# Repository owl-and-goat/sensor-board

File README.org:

#+title: sensor board

* stackup & antenna
see https://jlcpcb.com/impedance; stackup is currently set to 1.6 mm, controlled
impedance, 1 oz copper on all layers, which gives 0.203 mm / 0.008" outer
prepreg thickness for the "no requirement" stackup. board thickness is 1.6 mm ≈
0.062", so we'll be using the first of [[https://www.silabs.com/documents/public/application-notes/an1088-designing-with-pcb-antenna.pdf][these]] reference layouts.

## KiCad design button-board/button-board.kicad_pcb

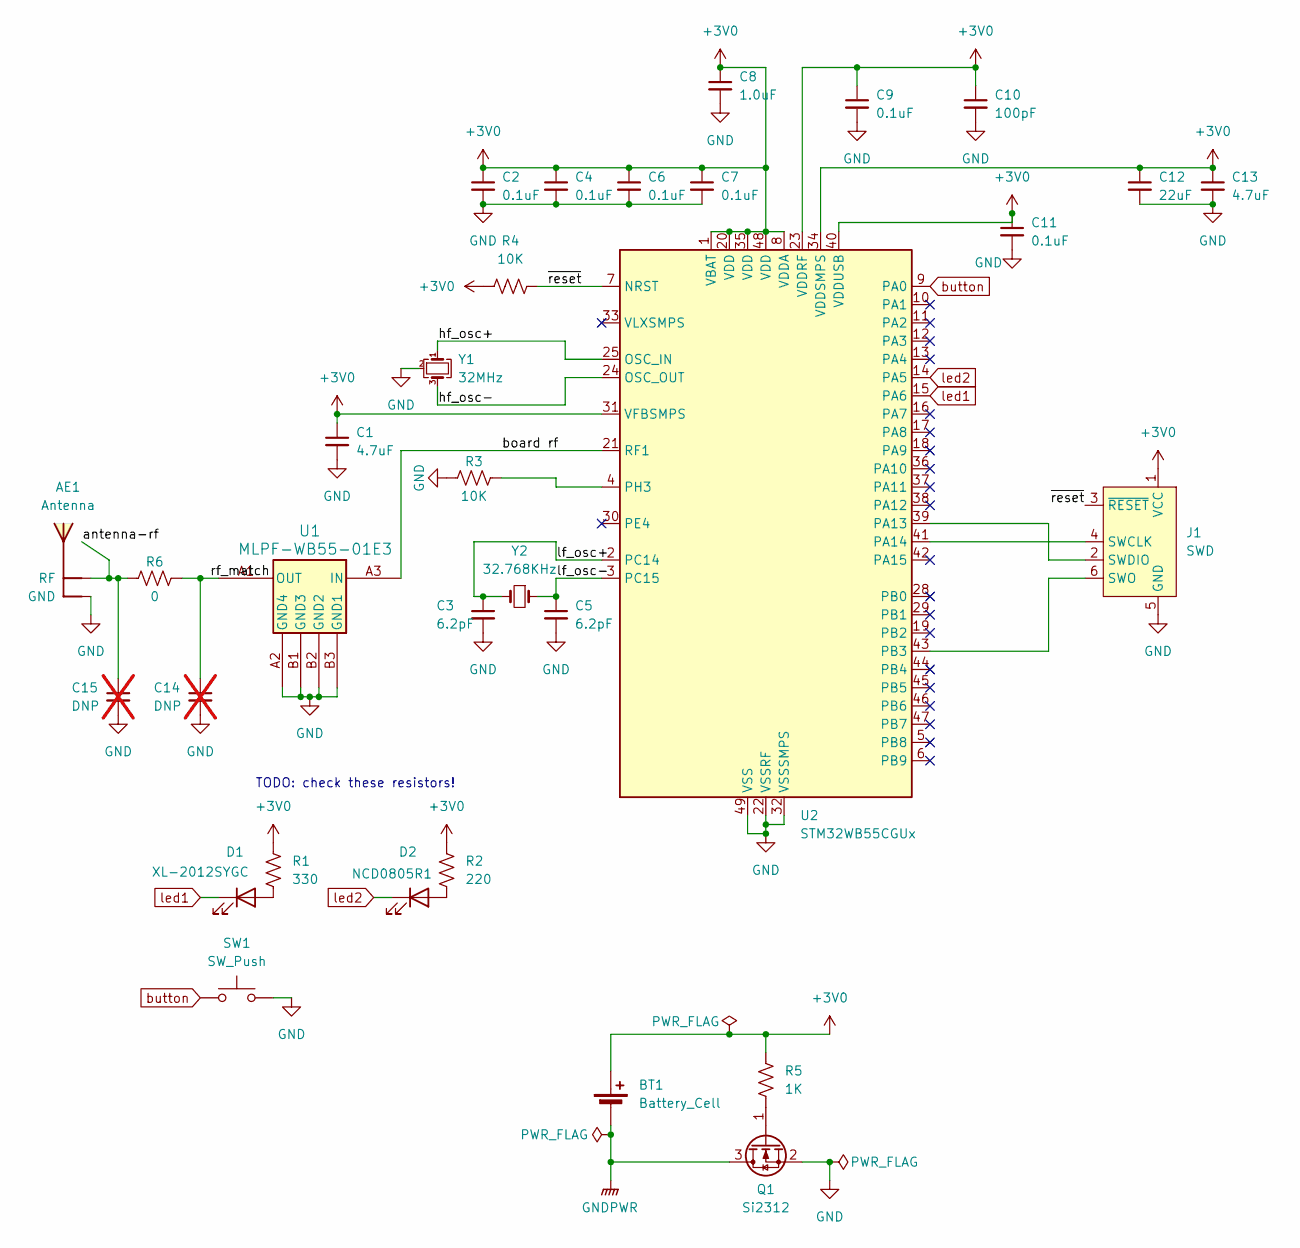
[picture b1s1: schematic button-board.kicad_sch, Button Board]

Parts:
AE1: Antenna; ANT_MIFA_TI_AN043
BT1: Battery_Cell; BatteryHolder_Keystone_3034_1x20mm_SmallPad
C1, C13: 4.7uF; C_0402_1005Metric; LCSC C23733
C2, C4, C6, C7, C9, C11: 0.1uF; C_0402_1005Metric; LCSC C141382
C3, C5: 6.2pF; C_0402_1005Metric
C8: 1.0uF; C_0402_1005Metric; LCSC C52923
C10: 100pF; C_0402_1005Metric; LCSC C1546
C12: 22uF; C_0805_2012Metric
C14, C15: DNP; C_0402_1005Metric; not fitted
D1: XL-2012SYGC; LED_0805_2012Metric; LCSC C965816
D2: NCD0805R1; LED_0805_2012Metric; LCSC C84256
J1: SWD; Tag-Connect_TC2030-IDC-NL_2x03_P1.27mm_Vertical
Q1: Si2312; SOT-23
R1: 330; R_0402_1005Metric; LCSC C25104
R2: 220; R_0402_1005Metric; LCSC C25091
R3, R4: 10K; R_0402_1005Metric; LCSC C25744
R5: 1K; R_0402_1005Metric; LCSC C11702
R6: 0; R_0402_1005Metric; LCSC C17168
SW1: SW_Push; Keystone_5133_KeypadDome_8mm
U1: MLPF-WB55-01E3; MLPF-WB55-01E3_STM; LCSC C2651048
U2: STM32WB55CGUx; QFN-48-1EP_7x7mm_P0.5mm_EP5.6x5.6mm; LCSC C404023
Y1: 32MHz; Crystal_SMD_2016-4Pin_2.0x1.6mm
Y2: 32.768KHz; Crystal_SMD_3215-2Pin_3.2x1.5mm

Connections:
+3V0: BT1.1 (+), C1.1, C2.1, C4.1, C6.1, C7.1, C8.1, C9.1, C10.1, C11.1, C12.1, C13.1, J1.1 (VCC), R1.1, R2.1, R4.1, R5.2, U2.1 (VBAT), U2.8 (VDDA), U2.20 (VDD), U2.23 (VDDRF), U2.31 (VFBSMPS), U2.34 (VDDSMPS), U2.35 (VDD), U2.40 (VDDUSB), U2.48 (VDD)
/antenna-rf: AE1.1 (RF), C15.1, R6.1
/board rf: U1.A3 (IN), U2.21 (RF1)
/hf_osc+: U2.25 (OSC_IN), Y1.1
/hf_osc-: U2.24 (OSC_OUT), Y1.3
/lf_osc+: C3.1, U2.2 (PC14), Y2.2
/lf_osc-: C5.1, U2.3 (PC15), Y2.1
/rf_match: C14.1, R6.2, U1.A1 (OUT)
/~reset: J1.3 (~RESET), R4.2, U2.7 (NRST)
GND: AE1.2 (GND), C1.2, C2.2, C3.2, C4.2, C5.2, C6.2, C7.2, C8.2, C9.2, C10.2, C11.2, C12.2, C13.2, C14.2, C15.2, J1.5 (GND), Q1.2 (S), R3.1, SW1.2, U1.A2 (GND4), U1.B1 (GND3), U1.B2 (GND2), U1.B3 (GND1), U2.22 (VSSRF), U2.32 (VSSSMPS), U2.49 (VSS), Y1.2 (G), Y1.4 (G)
GNDPWR: BT1.2 (-), Q1.3 (D)
unnamed: D1.2 (A), R1.2
unnamed: D2.2 (A), R2.2
unnamed: J1.4 (SWCLK), U2.41 (PA14)
unnamed: J1.2 (SWDIO), U2.39 (PA13)
unnamed: J1.6 (SWO), U2.43 (PB3)
unnamed: Q1.1 (G), R5.1
unnamed: R3.2, U2.4 (PH3)
button: SW1.1, U2.9 (PA0)
led1: D1.1 (K), U2.15 (PA6)
led2: D2.1 (K), U2.14 (PA5)

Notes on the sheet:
TODO: check these resistors!

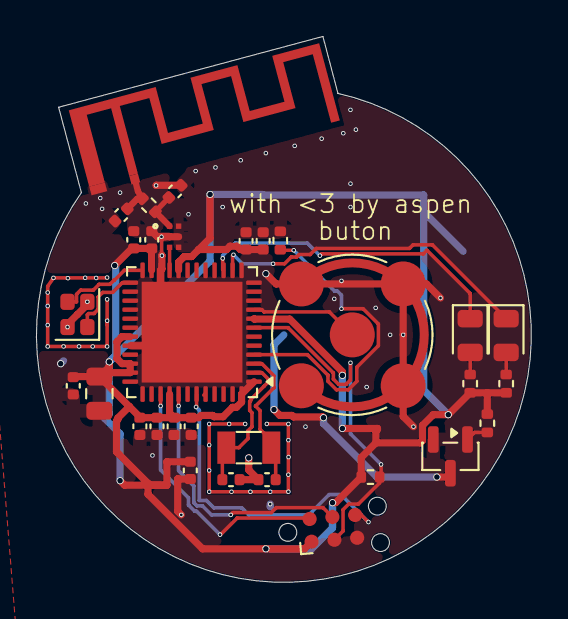
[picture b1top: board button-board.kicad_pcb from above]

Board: 4 copper layers, 27.5 x 30.3 mm, 32 parts (1 on the bottom side), 21 nets.

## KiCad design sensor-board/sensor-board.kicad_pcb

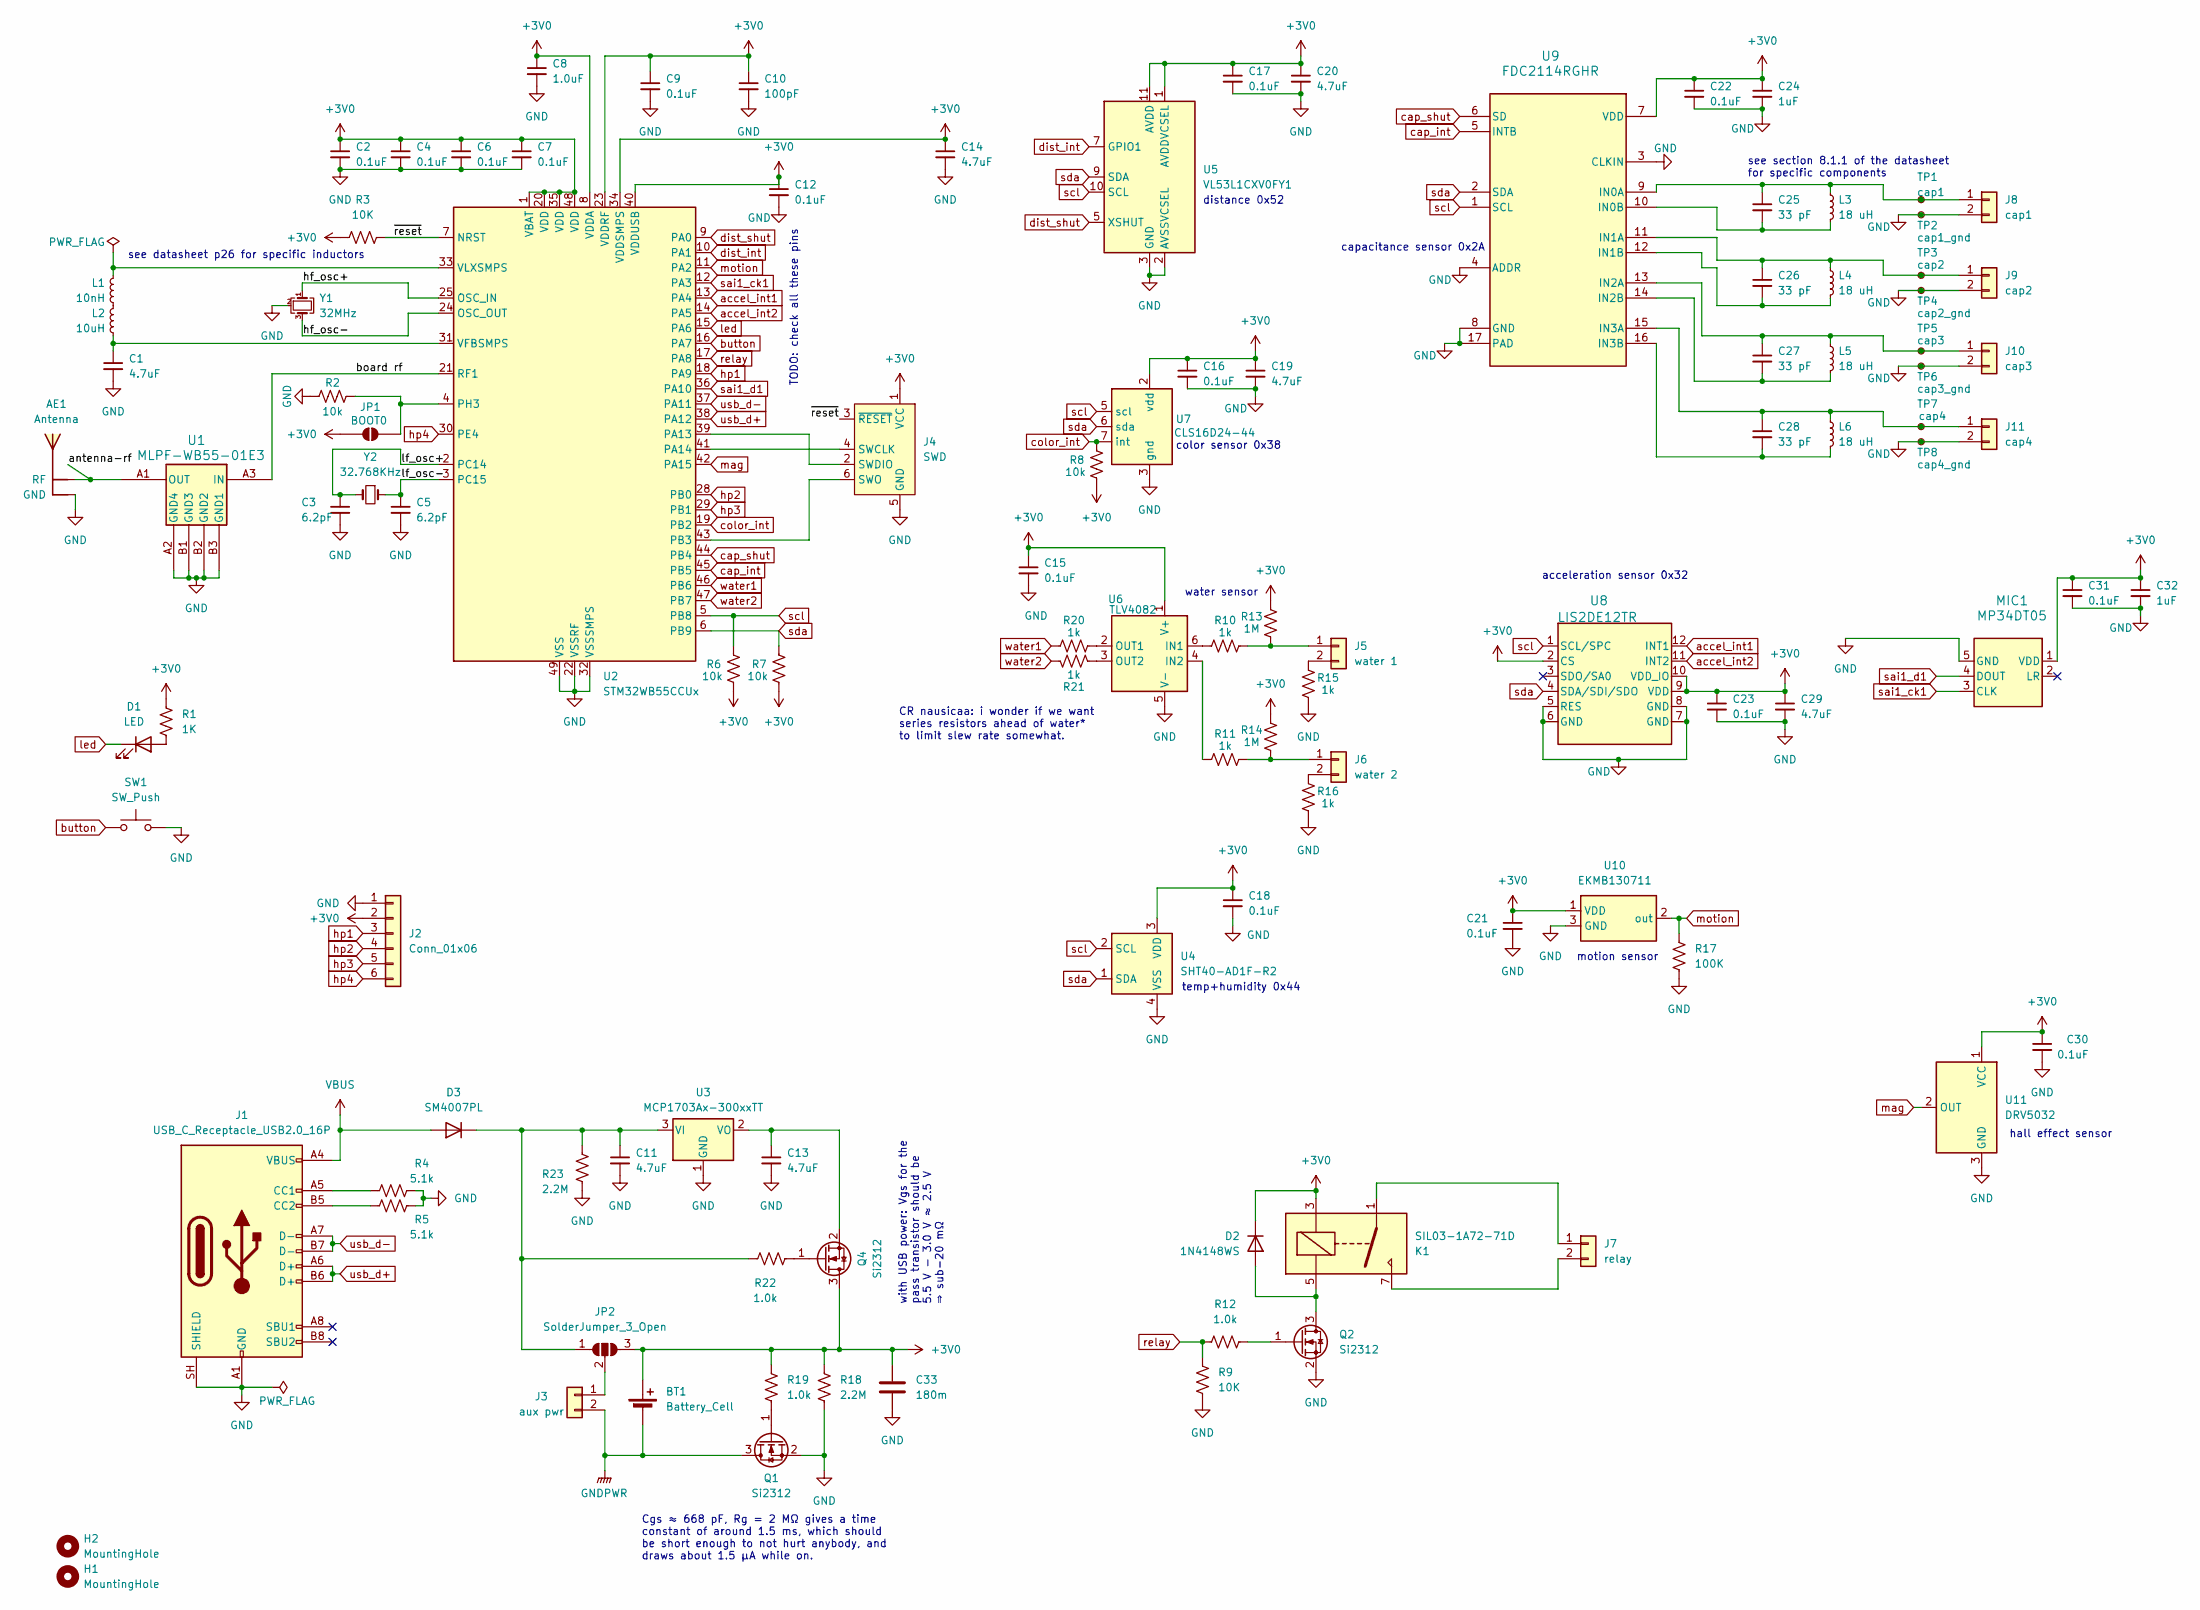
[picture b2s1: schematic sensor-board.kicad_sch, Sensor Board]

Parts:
AE1: Antenna; Antenna_2.4GHz_InvertedF_SiLabs
BT1: Battery_Cell; BatteryHolder_CR2032
C1, C13, C14, C19, C20, C29: 4.7uF; C_0402_1005Metric; LCSC C23733
C2, C4, C6, C7, C9, C12, C15, C16, C17, C18, C21, C22, C23, C30, C31: 0.1uF; C_0402_1005Metric; LCSC C141382
C3, C5: 6.2pF; C_0402_1005Metric
C8: 1.0uF; C_0402_1005Metric; LCSC C52923
C10: 100pF; C_0402_1005Metric; LCSC C1546
C11: 4.7uF; C_0805_2012Metric; LCSC C23733
C24, C32: 1uF; C_0402_1005Metric; LCSC C52923
C25, C26, C27, C28: 33 pF; C_0402_1005Metric; LCSC C1562
C33: 180m; PinHeader_1x02_P2.54mm_Vertical
D1: LED; LED_0805_2012Metric; LCSC C84256
D2: 1N4148WS; D_SOD-323; LCSC C2128
D3: SM4007PL; D_SMA
H1, H2: MountingHole; MountingHole_2.2mm_M2
J1: USB_C_Receptacle_USB2.0_16P; USB_C_Receptacle_G-Switch_GT-USB-7010ASV
J2: Conn_01x06; PinHeader_1x06_P2.54mm_Vertical
J3: aux pwr; JST_SH_BM02B-SRSS-TB_1x02-1MP_P1.00mm_Vertical
J4: SWD; Tag-Connect_TC2030-IDC-NL_2x03_P1.27mm_Vertical
J5: water 1; JST_SH_BM02B-SRSS-TB_1x02-1MP_P1.00mm_Vertical
J6: water 2; JST_SH_BM02B-SRSS-TB_1x02-1MP_P1.00mm_Vertical
J7: relay; JST_SH_BM02B-SRSS-TB_1x02-1MP_P1.00mm_Vertical
J8: cap1; JST_SH_BM02B-SRSS-TB_1x02-1MP_P1.00mm_Vertical
J9: cap2; JST_SH_BM02B-SRSS-TB_1x02-1MP_P1.00mm_Vertical
J10: cap3; JST_SH_BM02B-SRSS-TB_1x02-1MP_P1.00mm_Vertical
J11: cap4; JST_SH_BM02B-SRSS-TB_1x02-1MP_P1.00mm_Vertical
JP1: BOOT0; SolderJumper-2_P1.3mm_Open_RoundedPad1.0x1.5mm
JP2: SolderJumper_3_Open; SolderJumper-3_P1.3mm_Open_RoundedPad1.0x1.5mm
K1: SIL03-1A72-71D; SIL031A7271D
L1: 10nH; L_0402_1005Metric
L2: 10uH; L_0805_2012Metric
L3, L4, L5, L6: 18 uH; L_0603_1608Metric
MIC1: MP34DT05; HCLGA4_MP34_STM
Q1, Q2, Q4: Si2312; SOT-23
R1: 1K; R_0402_1005Metric; LCSC C11702
R2, R6, R7, R8: 10k; R_0402_1005Metric; LCSC C25744
R3, R9: 10K; R_0402_1005Metric; LCSC C25744
R4, R5: 5.1k; R_0402_1005Metric; LCSC C25905
R10, R11, R15, R16, R20, R21: 1k; R_0402_1005Metric; LCSC C11702
R12, R19, R22: 1.0k; R_0402_1005Metric; LCSC C11702
R13, R14: 1M; R_0402_1005Metric; LCSC C26083
R17: 100K; R_0402_1005Metric; LCSC C25741
R18, R23: 2.2M; R_0603_1608Metric; LCSC C22938
SW1: SW_Push; SW_SPST_TS-1088-xR020; LCSC C720477
TP1: cap1; TestPoint_Pad_1.0x1.0mm
TP2: cap1_gnd; TestPoint_Pad_1.0x1.0mm
TP3: cap2; TestPoint_Pad_1.0x1.0mm
TP4: cap2_gnd; TestPoint_Pad_1.0x1.0mm
TP5: cap3; TestPoint_Pad_1.0x1.0mm
TP6: cap3_gnd; TestPoint_Pad_1.0x1.0mm
TP7: cap4; TestPoint_Pad_1.0x1.0mm
TP8: cap4_gnd; TestPoint_Pad_1.0x1.0mm
U1: MLPF-WB55-01E3; MLPF-WB55-01E3_STM; LCSC C2651048
U2: STM32WB55CCUx; QFN-48-1EP_7x7mm_P0.5mm_EP5.6x5.6mm; LCSC C404023
U3: MCP1703Ax-300xxTT; SOT-23; LCSC C625372
U4: SHT40-AD1F-R2; Sensirion_DFN-4_1.5x1.5mm_P0.8mm_SHT4x_NoCentralPad
U5: VL53L1CXV0FY1; ST_VL53L1x
U6: TLV4082; SOT-23-6
U7: CLS16D24-44; CLS-16D24-44-DF8TR8
U8: LIS2DE12TR; LGA-12_STM
U9: FDC2114RGHR
U10: EKMB130711; EKMB1307111K
U11: DRV5032; SOT-23
Y1: 32MHz; Crystal_SMD_2016-4Pin_2.0x1.6mm
Y2: 32.768KHz; Crystal_SMD_3215-2Pin_3.2x1.5mm

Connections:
+3V0: BT1.1 (+), C2.1, C4.1, C6.1, C7.1, C8.1, C9.1, C10.1, C12.1, C14.1, C15.1, C16.1, C17.1, C18.1, C19.1, C20.1, C21.1, C22.1, C23.1, C24.1, C29.1, C30.1, C31.1, C32.1, C33.1, D2.1 (K), J2.2, J4.1 (VCC), JP1.1 (A), JP2.3 (B), K1.3, MIC1.1 (VDD), Q4.3 (D), R1.1, R3.1, R6.1, R7.1, R8.1, R13.2, R14.2, R18.1, R19.2, U2.1 (VBAT), U2.8 (VDDA), U2.20 (VDD), U2.23 (VDDRF), U2.34 (VDDSMPS), U2.35 (VDD), U2.40 (VDDUSB), U2.48 (VDD), U4.3 (VDD), U5.1 (AVDDVCSEL), U5.11 (AVDD), U6.1 (V+), U7.2 (vdd), U8.2 (CS), U8.9 (VDD), U8.10 (VDD_IO), U9.7 (VDD), U10.1 (VDD), U11.1 (VCC)
/antenna-rf: AE1.1 (RF), U1.A1 (OUT)
/board rf: U1.A3 (IN), U2.21 (RF1)
/hf_osc+: U2.25 (OSC_IN), Y1.1
/hf_osc-: U2.24 (OSC_OUT), Y1.3
/lf_osc+: C3.1, U2.2 (PC14), Y2.2
/lf_osc-: C5.1, U2.3 (PC15), Y2.1
/~reset: J4.3 (~RESET), R3.2, U2.7 (NRST)
GND: AE1.2 (GND), C1.2, C2.2, C3.2, C4.2, C5.2, C6.2, C7.2, C8.2, C9.2, C10.2, C11.2, C12.2, C13.2, C14.2, C15.2, C16.2, C17.2, C18.2, C19.2, C20.2, C21.2, C22.2, C23.2, C24.2, C29.2, C30.2, C31.2, C32.2, C33.2, J1.A1 (GND), J1.A12 (GND), J1.B1 (GND), J1.B12 (GND), J1.SH (SHIELD), J2.1, J4.5 (GND), J8.2, J9.2, J10.2, J11.2, MIC1.5 (GND), Q1.2 (S), Q2.2 (S), R2.1, R4.2, R5.2, R9.1, R15.1, R16.1, R17.2, R18.2, R23.2, SW1.2, TP2.1 (1_1), TP4.1 (1_1), TP6.1 (1_1), TP8.1 (1_1), U1.A2 (GND4), U1.B1 (GND3), U1.B2 (GND2), U1.B3 (GND1), U2.22 (VSSRF), U2.32 (VSSSMPS), U2.49 (VSS), U3.1 (GND), U4.4 (VSS), U5.2 (AVSSVCSEL), U5.3 (GND), U5.4 (GND), U5.6 (GND), U5.12 (GND), U6.5 (V-), U7.3 (gnd), U8.5 (RES), U8.6 (GND), U8.7 (GND), U8.8 (GND), U9.3 (CLKIN), U9.4 (ADDR), U9.8 (GND), U9.17 (PAD), U10.3 (GND), U11.3 (GND), Y1.2 (G), Y1.4 (G)
GNDPWR: BT1.2 (-), J3.2, Q1.3 (D)
unnamed: D1.2 (A), R1.2
unnamed: D2.2 (A), K1.5, Q2.3 (D)
unnamed: C11.1, D3.1 (K), JP2.1 (A), R22.1, R23.1, U3.3 (VI)
unnamed: J1.A5 (CC1), R4.1
unnamed: J1.B5 (CC2), R5.1
unnamed: J3.1, JP2.2 (C)
unnamed: J4.4 (SWCLK), U2.41 (PA14)
unnamed: J4.2 (SWDIO), U2.39 (PA13)
unnamed: J4.6 (SWO), U2.43 (PB3)
unnamed: J5.1, R10.2, R13.1
unnamed: J5.2, R15.2
unnamed: J6.1, R11.2, R14.1
unnamed: J6.2, R16.2
unnamed: J7.1, K1.1
unnamed: J7.2, K1.7
unnamed: C25.1, J8.1, L3.1, TP1.1 (1_1), U9.9 (IN0A)
unnamed: C26.1, J9.1, L4.1, TP3.1 (1_1), U9.11 (IN1A)
unnamed: C27.1, J10.1, L5.1, TP5.1 (1_1), U9.13 (IN2A)
unnamed: C28.1, J11.1, L6.1, TP7.1 (1_1), U9.15 (IN3A)
unnamed: JP1.2 (B), R2.2, U2.4 (PH3)
unnamed: L1.2, L2.1
unnamed: Q1.1 (G), R19.1
unnamed: Q2.1 (G), R12.2
unnamed: Q4.1 (G), R22.2
unnamed: C13.1, Q4.2 (S), U3.2 (VO)
unnamed: C1.1, L2.2, U2.31 (VFBSMPS)
unnamed: L1.1, U2.33 (VLXSMPS)
unnamed: R10.1, U6.6 (IN1)
unnamed: R11.1, U6.4 (IN2)
unnamed: R20.2, U6.2 (OUT1)
unnamed: R21.2, U6.3 (OUT2)
unnamed: C25.2, L3.2, U9.10 (IN0B)
unnamed: C26.2, L4.2, U9.12 (IN1B)
unnamed: C27.2, L5.2, U9.14 (IN2B)
unnamed: C28.2, L6.2, U9.16 (IN3B)
VBUS: D3.2 (A), J1.A4 (VBUS), J1.A9 (VBUS), J1.B4 (VBUS), J1.B9 (VBUS)
accel_int1: U2.13 (PA4), U8.12 (INT1)
accel_int2: U2.14 (PA5), U8.11 (INT2)
button: SW1.1, U2.16 (PA7)
cap_int: U2.45 (PB5), U9.5 (INTB)
cap_shut: U2.44 (PB4), U9.6 (SD)
color_int: R8.2, U2.19 (PB2), U7.7 (int)
dist_int: U2.10 (PA1), U5.7 (GPIO1)
dist_shut: U2.9 (PA0), U5.5 (XSHUT)
hp1: J2.3, U2.18 (PA9)
hp2: J2.4, U2.28 (PB0)
hp3: J2.5, U2.29 (PB1)
hp4: J2.6, U2.30 (PE4)
led: D1.1 (K), U2.15 (PA6)
mag: U2.42 (PA15), U11.2 (OUT)
motion: R17.1, U2.11 (PA2), U10.2 (out)
relay: R9.2, R12.1, U2.17 (PA8)
sai1_ck1: MIC1.3 (CLK), U2.12 (PA3)
sai1_d1: MIC1.4 (DOUT), U2.36 (PA10)
scl: R6.2, U2.5 (PB8), U4.2 (SCL), U5.10 (SCL), U7.5 (scl), U8.1 (SCL/SPC), U9.1 (SCL)
sda: R7.2, U2.6 (PB9), U4.1 (SDA), U5.9 (SDA), U7.6 (sda), U8.4 (SDA/SDI/SDO), U9.2 (SDA)
usb_d+: J1.A6 (D+), J1.B6 (D+), U2.38 (PA12)
usb_d-: J1.A7 (D-), J1.B7 (D-), U2.37 (PA11)
water1: R20.1, U2.46 (PB6)
water2: R21.1, U2.47 (PB7)

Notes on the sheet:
temp+humidity 0x44
with USB power: Vgs for the pass transistor should be 5.5 V - 3.0 V ≈ 2.5 V ⇒ sub-20 mΩ
color sensor 0x38
motion sensor
acceleration sensor 0x32
CR nausicaa: i wonder if we want series resistors ahead of water* to limit slew rate somewhat.
see section 8.1.1 of the datasheet for specific components
hall effect sensor
water sensor
see datasheet p26 for specific inductors
TODO: check all these pins
Cgs ≈ 668 pF, Rg = 2 MΩ gives a time constant of around 1.5 ms, which should be short enough to not hurt anybody, and draws about 1.5 μA while on.
capacitance sensor 0x2A
distance 0x52

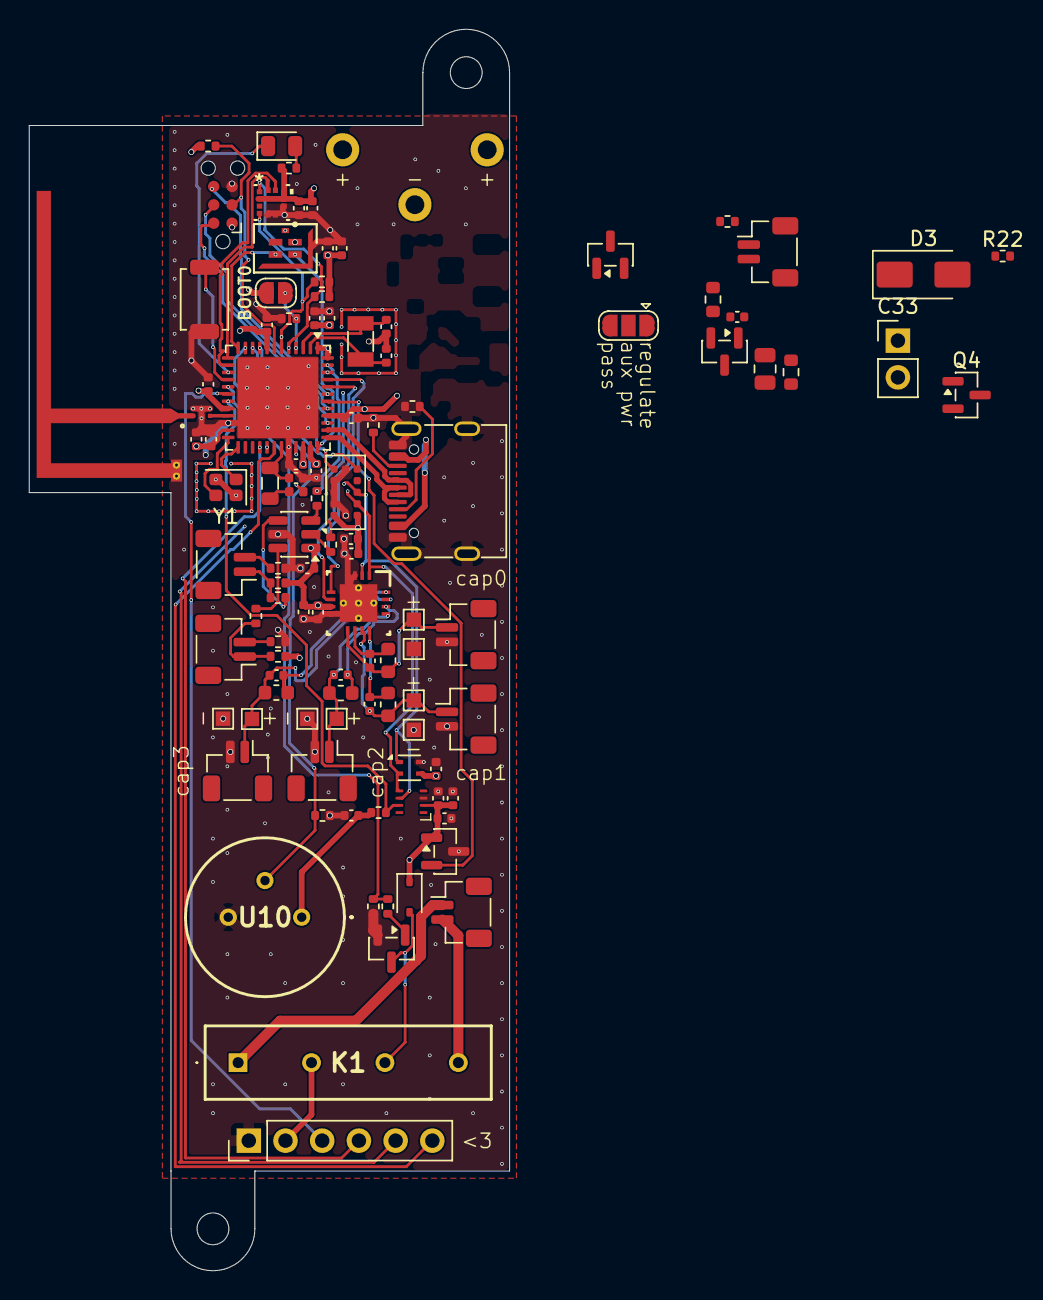
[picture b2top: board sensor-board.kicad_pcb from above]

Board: 4 copper layers, 33.2 x 85.9 mm, 109 parts (0 on the bottom side), 70 nets.

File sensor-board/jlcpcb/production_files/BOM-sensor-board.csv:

Comment,Designator,Footprint,LCSC,Quantity
0.1uF,"C12,C15,C16,C17,C18,C2,C21,C22,C23,C30,C31,C4,C6,C7,C9",C_0402_1005Metric,C141382,15
1.0k,"R12,R19",R_0402_1005Metric,C11702,2
1.0uF,C8,C_0402_1005Metric,C52923,1
100K,R17,R_0402_1005Metric,C25741,1
100pF,C10,C_0402_1005Metric,C1546,1
10K,"R3,R9",R_0402_1005Metric,C25744,2
10k,"R2,R6,R7,R8",R_0402_1005Metric,C25744,4
10nH,L1,L_0402_1005Metric,C3911026,1
10uH,L2,L_0805_2012Metric,C162582,1
18 uH,"L3,L4,L5,L6",L_0603_1608Metric,C275349,4
1K,R1,R_0402_1005Metric,C11702,1
1M,"R13,R14",R_0402_1005Metric,C26083,2
1N4148WS,D2,D_SOD-323,C2128,1
1k,"R10,R11,R15,R16,R20,R21",R_0402_1005Metric,C11702,6
1uF,"C24,C32",C_0402_1005Metric,C52923,2
2.2M,R18,R_0603_1608Metric,C22938,1
32.768KHz,Y2,Crystal_SMD_3215-2Pin_3.2x1.5mm,C94673,1
32MHz,Y1,Crystal_SMD_2016-4Pin_2.0x1.6mm,C843260,1
33 pF,"C25,C26,C27,C28",C_0402_1005Metric,C1562,4
4.7uF,"C1,C11,C13,C14,C19,C20,C29",C_0402_1005Metric,C23733,7
5.1k,"R4,R5",R_0402_1005Metric,C25905,2
6.2pF,"C3,C5",C_0402_1005Metric,C82154,2
LED,D1,LED_0805_2012Metric,C84256,1
MCP1703Ax-300xxTT,U3,SOT-23,C625372,1
MLPF-WB55-01E3,U1,MLPF-WB55-01E3_STM,C2651048,1
STM32WB55CCUx,U2,QFN-48-1EP_7x7mm_P0.5mm_EP5.6x5.6mm,C404023,1
SW_Push,SW1,SW_SPST_TS-1088-xR020,C720477,1
Si2312,"Q1,Q2",SOT-23,C142518,2
USB_C_Receptacle_USB2.0_16P,J1,USB_C_Receptacle_G-Switch_GT-USB-7010ASV,C2988369,1

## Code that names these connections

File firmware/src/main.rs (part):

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        PowerMode::Aux => {
            let (usb_device, link) = usb::Builder {
                usb: p.USB,
                dp: p.PA12,
                dm: p.PA11,
            }
            .init();
            spawner.spawn(usb(usb_device).unwrap());
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        PowerMode::Battery => None,
    };

    let scl = p.PB8;
    let sda = p.PB9;
    let mut config = i2c::Config::default();
    config.timeout = Duration::from_millis(10);

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    )));

    static CAPACITANCE: StaticCell<sensor::Shared<CapacitanceSensor<'static>>> = StaticCell::new();
    let capacitance = match CapacitanceSensor::init(p.PB4, i2c).await {
        Ok(sensor) => Some(&*CAPACITANCE.init(Mutex::new(sensor))),
        Err(e) => {
            defmt::warn!("capacitance sensor failed to initialize: {}", e);
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    static MIC_BUF: StaticCell<[u8; 512]> = StaticCell::new();
    let pdm = Pdm::new(
        p.SAI1,
        p.PA3,
        p.PA10,
        pdm::Channel::Right,
        p.DMA1_CH2,
        Irqs,
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    let mic = &*MIC.init(Mutex::new(Mic::new(pdm)));

    let (motion_task, motion_monitor) = motion::Builder {
        pin: p.PA2,
        exti: p.EXTI2,
    }
    .init();
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    spawner.spawn(discovery(discovery_task, publisher).unwrap());

    let button_task = button::Builder {
        button: p.PA7,
        exti: p.EXTI7,
        led: p.PA6,
        config: config_eraser,
    }
    .init();
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
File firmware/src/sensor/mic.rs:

//! MEMS microphone (MP34DT05): the sound level, measured on request.
//!
//! The microphone is on SAI1's PDM interface (`pdm`): SAI1_CK1 (PA3) clocks
//! it and its data comes in on SAI1_D1 (PA10). Its L/R pin is left floating,
//! which its pull-down makes GND: the right microphone of the pair. The
//! interface is on only while a measurement lasts; with no clock the
//! microphone is in power-down.
//!
//! SAI1's kernel clock is PLLSAI1 at 8.192 MHz (`configure_clocks` in
//! `main.rs`), which divides down to a bitstream clock of 2.048 MHz (1.2 to
//! 3.25 MHz in the microphone's datasheet). `filter` decimates that by 128,
//! to 16 kHz.

use embassy_time::{Duration, Instant};
use protocol::{SensorReadError, SoundLevel, SoundLevelResult};

mod filter;
pub mod pdm;

use filter::Filter;
use pdm::Pdm;

/// PCM samples per second.
const RATE: u64 = 16_000;
/// What is left out at the start of a measurement, and after an overrun:
/// the microphone's turn-on time (10 ms) and the high-pass filter's settling.
const SETTLE: Duration = Duration::from_millis(100);
/// PCM samples worked out at a time.
const CHUNK: usize = 16;

/// The PCM's RMS at 94 dB SPL. The microphone's sensitivity is -26 dBFS
/// (±3 dB) there, and the PCM's full scale is 12 dB below the bitstream's.
const RMS_AT_94_DB: f32 = 4620.0;

pub struct Mic<'d> {
    pdm: Pdm<'d>,
    filter: Filter,
}

impl<'d> Mic<'d> {
    pub fn new(pdm: Pdm<'d>) -> Self {
        Self {
            pdm,
            filter: Filter::new(),
        }
    }

    /// Turns the microphone on, listens for `duration`, and turns it off.
    /// The level is the RMS of the PCM, in dB SPL. A measurement that takes
    /// twice as long as it should has fallen behind the microphone, and is
    /// given up.
    pub async fn measure(&mut self, duration: Duration) -> SoundLevelResult {
        let samples = RATE * duration.as_micros() / 1_000_000;
        let settle = RATE * SETTLE.as_micros() / 1_000_000;

        let mut pdm = [0u8; CHUNK * filter::BYTES_PER_SAMPLE];
        let mut pcm = [0i16; CHUNK];
        let (mut sum, mut n) = (0u64, 0u64);
        let mut skip = settle;
        let mut overruns = 0u32;

        let deadline = Instant::now() + (SETTLE + duration) * 2;
        self.filter.reset();
        let mut capture = self.pdm.start();
        while n < samples && Instant::now() < deadline {
            if capture.read(&mut pdm).await.is_err() {
                overruns += 1;
                self.filter.reset();
                skip = settle;
                continue;
            }
            self.filter.process(&pdm, &mut pcm);
            for &x in &pcm {
                if skip > 0 {
                    skip -= 1;
                } else {
                    sum += (x as i32 * x as i32) as u64;
                    n += 1;
                }
            }
        }
        drop(capture);

        if overruns > 0 {
            defmt::warn!("mic: {} overruns during a measurement", overruns);
        }
        if n < samples {
            return Err(SensorReadError::MicOverrun);
        }
        let mean_square = (sum / n).max(1) as f32;
        Ok(SoundLevel {
            leq: 94.0 + 10.0 * libm::log10f(mean_square / (RMS_AT_94_DB * RMS_AT_94_DB)),
        })
    }
}
